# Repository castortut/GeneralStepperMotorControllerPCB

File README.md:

# GeneralStepperMotorControllerPCB
Designed for can opener. Uses Arduino Nano and drv8825 / A4988

# TODO
- The power supply pins are the wrong way around in the PCB!

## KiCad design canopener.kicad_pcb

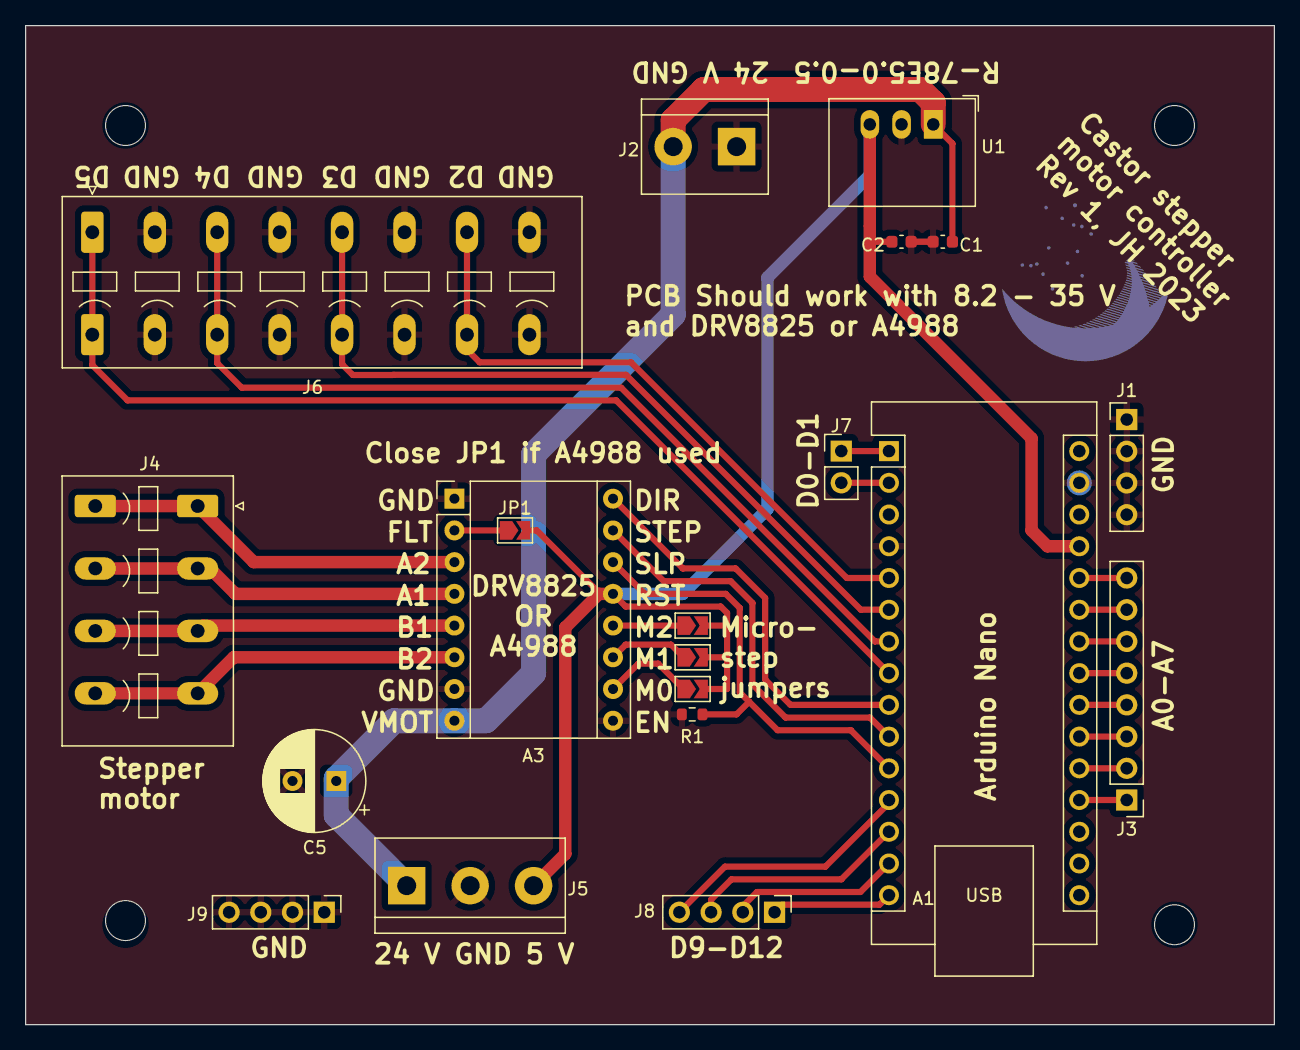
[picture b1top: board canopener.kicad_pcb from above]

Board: 2 copper layers, 100.0 x 80.0 mm, 25 parts (1 on the bottom side), 32 nets.

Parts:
A1: Arduino_Nano_v3.x; Arduino_Nano
A3: Pololu_Breakout_DRV8825; Pololu_Breakout-16_15.2x20.3mm
C1, C2: 10u; C_0603_1608Metric
C5: 100u; CP_Radial_D8.0mm_P3.50mm
H1, H2, H3, H4: MountingHole; MountingHole_3.2mm_M3
J1, J8, J9: Conn_01x04; PinHeader_1x04_P2.54mm_Vertical
J2: Screw_Terminal_01x02; TerminalBlock_bornier-2_P5.08mm
J3: Conn_01x08; PinHeader_1x08_P2.54mm_Vertical
J4: Screw_Terminal_01x04; PhoenixContact_SPT_2.5_4-V-5.0-EX_1x04_P5.0mm_Vertical
J5: Screw_Terminal_01x03; TerminalBlock_bornier-3_P5.08mm
J6: Screw_Terminal_01x08; PhoenixContact_SPT_2.5_8-V-5.0-EX_1x08_P5.0mm_Vertical
J7: Conn_01x02; PinHeader_1x02_P2.54mm_Vertical
JP1: Jumper_2_Open; SolderJumper-2_P1.3mm_Open_TrianglePad1.0x1.5mm
LOGO1: CASTOR; Castor logo
M0, M1, M2: Jumper_2_Open; SolderJumper-2_P1.3mm_Open_TrianglePad1.0x1.5mm
R1: R; R_0603_1608Metric
U1: R-78E5.0-0.5; Converter_DCDC_RECOM_R-78E-0.5_THT

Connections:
+5V: A1.27 (+5V), A3.13 (~RST), C2.1, J5.3, JP1.2 (B), M0.2 (B), M1.2 (B), M2.2 (B), U1.3 (OUT)
+24V: A3.8 (VMOT), C1.1, C5.1, J2.2, J5.1, U1.1 (IN)
GND: A1.4 (GND), A1.29 (GND), A3.1 (GND), A3.7 (GND), A3.9 (~EN), C1.2, C2.2, C5.2, J1.1, J1.2, J1.3, J1.4, J2.1, J5.2, J6.2, J6.4, J6.6, J6.8, J9.1, J9.2, J9.3, J9.4, R1.2, U1.2 (GND)
unnamed: A1.19 (A0), J3.1
unnamed: A1.20 (A1), J3.2
unnamed: A1.21 (A2), J3.3
unnamed: A1.22 (A3), J3.4
unnamed: A1.23 (A4), J3.5
unnamed: A1.24 (A5), J3.6
unnamed: A1.25 (A6), J3.7
unnamed: A1.26 (A7), J3.8
unnamed: A1.2 (D0/RX), J7.2
unnamed: A1.1 (D1/TX), J7.1
unnamed: A1.5 (D2), J6.7
unnamed: A1.6 (D3), J6.5
unnamed: A1.7 (D4), J6.3
unnamed: A1.8 (D5), J6.1
unnamed: A1.9 (D6), A3.16 (DIR)
unnamed: A1.10 (D7), A3.15 (STEP)
unnamed: A1.11 (D8), A3.14 (~SLP), R1.1
unnamed: A1.12 (D9), J8.4
unnamed: A1.13 (D10), J8.3
unnamed: A1.14 (D11), J8.2
unnamed: A1.15 (D12), J8.1
unnamed: A3.4 (A1), J4.2
unnamed: A3.3 (A2), J4.1
unnamed: A3.5 (B1), J4.3
unnamed: A3.6 (B2), J4.4
unnamed: A3.10 (M0), M0.1 (A)
unnamed: A3.11 (M1), M1.1 (A)
unnamed: A3.12 (M2), M2.1 (A)
unnamed: A3.2 (~FLT), JP1.1 (A)

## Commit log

2023-04-14 Add Kicad files
2023-04-16 Better version. Added also documentation
2023-04-16 Maybe ready :D
2023-04-24 add a small logo
2023-08-17 Added Arduino code
2023-08-23 Small code changes
